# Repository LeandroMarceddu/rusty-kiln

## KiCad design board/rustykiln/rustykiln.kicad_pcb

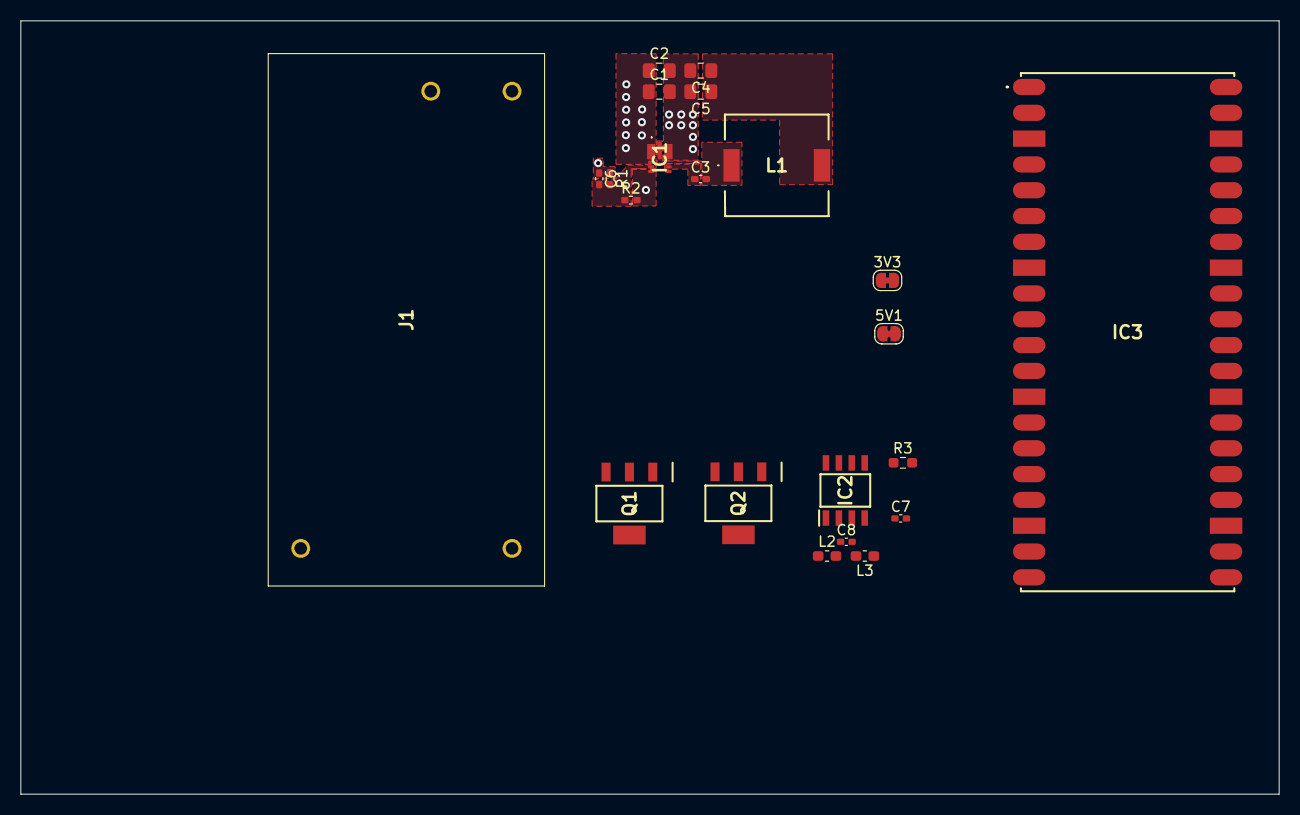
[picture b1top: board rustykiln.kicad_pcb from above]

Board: 4 copper layers, 123.8 x 76.1 mm, 22 parts (0 on the bottom side), 15 nets, no tracks yet.

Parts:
3V3, 5V1: SolderJumper_2_Bridged; SolderJumper-2_P1.3mm_Bridged_RoundedPad1.0x1.5mm
C1, C2: 4.7uF; C_0805_2012Metric_Pad1.18x1.45mm_HandSolder
C3, C7: 0.1uF; C_0402_1005Metric_Pad0.74x0.62mm_HandSolder
C4, C5: 22uF; C_0805_2012Metric_Pad1.18x1.45mm_HandSolder
C6: 47pF; C_0402_1005Metric_Pad0.74x0.62mm_HandSolder
C8: 10nF; C_0402_1005Metric_Pad0.74x0.62mm_HandSolder
IC1: AP63357DV-7; AP63357DV7
IC2: MAX31855KASA+T; SOIC127P600X175-8N
IC3: RASPBERRY_PI_PICO_W; RASPBERRYPIPICOW
J1: MPM-15-24; MPM1524
L1: 6.8uH; CDRH103RNP6R8NCB
L2, L3: 470Ohm; L_0603_1608Metric_Pad1.05x0.95mm_HandSolder
Q1, Q2: ZXMS6006SGTA; SOT230P700X170-4N
R1: 220K; R_0402_1005Metric_Pad0.72x0.64mm_HandSolder
R2: 41.2K; R_0402_1005Metric_Pad0.72x0.64mm_HandSolder
R3: 10k; R_0603_1608Metric_Pad0.98x0.95mm_HandSolder

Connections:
3V3: 3V3.1 (A), C7.1, IC2.4 (VCC), IC3.36 (3V3(OUT)), R3.2
5V: 5V1.1 (A), C4.1, C5.1, C6.1, IC3.39 (VSYS), L1.2, R1.1
24V: C1.1, C2.1, IC1.1 (VIN), IC1.2 (EN), J1.1 (+V), Q1.3 (S_1), Q1.4 (S_2), Q2.3 (S_1), Q2.4 (S_2)
/Power/BST: C3.1, IC1.6 (BST)
/Power/FB: C6.2, IC1.3 (FB), R1.2, R2.1
/Power/SW: C3.2, IC1.9 (SW), L1.1
CS: IC2.6 (~CS), IC3.17 (UART0_RX/I2C0_SCL_/SPI1_CSN/GP13), R3.1
GND: C1.2, C2.2, C4.2, C5.2, C7.2, IC1.4 (COMP), IC1.8 (GND), IC2.1 (GND), IC3.3 (GND_1), IC3.8 (GND_2), IC3.13 (GND_3), IC3.18 (GND_4), IC3.23 (GND_5), IC3.28 (GND_6), IC3.33 (GND/AGND), IC3.38 (GND_7), J1.2 (-V), R2.2
unnamed: 3V3.2 (B), 5V1.2 (B)
unnamed: C8.2, IC2.3 (T+), L3.2
unnamed: C8.1, IC2.2 (T-), L2.2
PWM1: IC3.19 (I2C1_SDA/SPI1_SCK/GP14), Q1.1 (IN)
PWM2: IC3.20 (I2C1_SCL/SPI1_TX/GP15), Q2.1 (IN)
SCK: IC2.5 (SCK), IC3.14 (I2C1_SDA_/SPI1__SCK/GP10)
SO: IC2.7 (SO), IC3.16 (UART0_TX/I2C0_SDA_/SPI1_RX_/GP12)

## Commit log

2022-09-24 first github push
2022-09-24 edit
2022-09-26 bare minimum I guess?
2022-09-26 Comment out more stuff
2022-10-18 Fast-forward
2023-05-21 Fresh start
2023-05-21 push
2023-05-21 Load with embassy example + satisfy rust_analyzer
2023-05-21 Fix the CI thing
2023-05-21 Remove linting and --release.
2023-05-28 cyw43 example wifi_scan
2023-05-28 release flags
2023-05-28 I'm an idiot
2023-05-28 Receiving :80 ok - need to check how to display
